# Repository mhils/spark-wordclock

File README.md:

spark-wordclock
===============

A Word Clock using the Spark Core.
https://community.spark.io/t/show-spark-wordclock-project/2347/

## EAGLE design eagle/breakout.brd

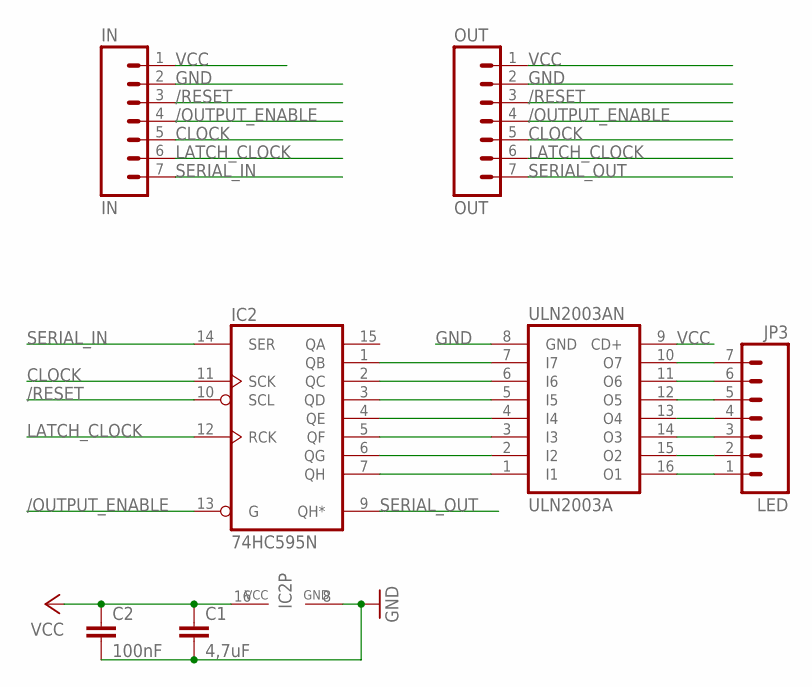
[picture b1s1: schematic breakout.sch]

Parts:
C1: 4,7uF; C025-024X044
C2: 100nF; C025-024X044
IC2: 74HC595N; DIL16
IN: IN; 1X07
JP3: LED; 1X07
OUT: OUT; 1X07
ULN2003A: ULN2003AN; DIL16

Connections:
/OUTPUT_ENABLE: IC2.13 (G), IN.4, OUT.4
/RESET: IC2.10 (SCL), IN.3, OUT.3
CLOCK: IC2.11 (SCK), IN.5, OUT.5
GND: C1.2, C2.2, IC2.8 (GND), IN.2, OUT.2, ULN2003A.8 (GND)
LATCH_CLOCK: IC2.12 (RCK), IN.6, OUT.6
unnamed: IC2.1 (QB), ULN2003A.7 (I7)
unnamed: IC2.2 (QC), ULN2003A.6 (I6)
unnamed: IC2.3 (QD), ULN2003A.5 (I5)
unnamed: IC2.4 (QE), ULN2003A.4 (I4)
unnamed: IC2.5 (QF), ULN2003A.3 (I3)
unnamed: IC2.6 (QG), ULN2003A.2 (I2)
unnamed: IC2.7 (QH), ULN2003A.1 (I1)
unnamed: JP3.7, ULN2003A.10 (O7)
unnamed: JP3.6, ULN2003A.11 (O6)
unnamed: JP3.5, ULN2003A.12 (O5)
unnamed: JP3.4, ULN2003A.13 (O4)
unnamed: JP3.3, ULN2003A.14 (O3)
unnamed: JP3.2, ULN2003A.15 (O2)
unnamed: JP3.1, ULN2003A.16 (O1)
SERIAL_IN: IC2.14 (SER), IN.7
SERIAL_OUT: IC2.9 (QH*), OUT.7
VCC: C1.1, C2.1, IC2.16 (VCC), IN.1, OUT.1, ULN2003A.9 (CD+)

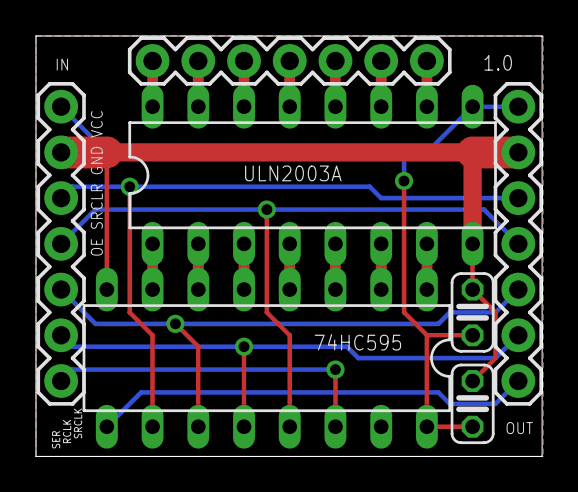
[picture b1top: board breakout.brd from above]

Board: 2 copper layers, 28.1 x 23.4 mm, 7 parts (0 on the bottom side), 22 nets.

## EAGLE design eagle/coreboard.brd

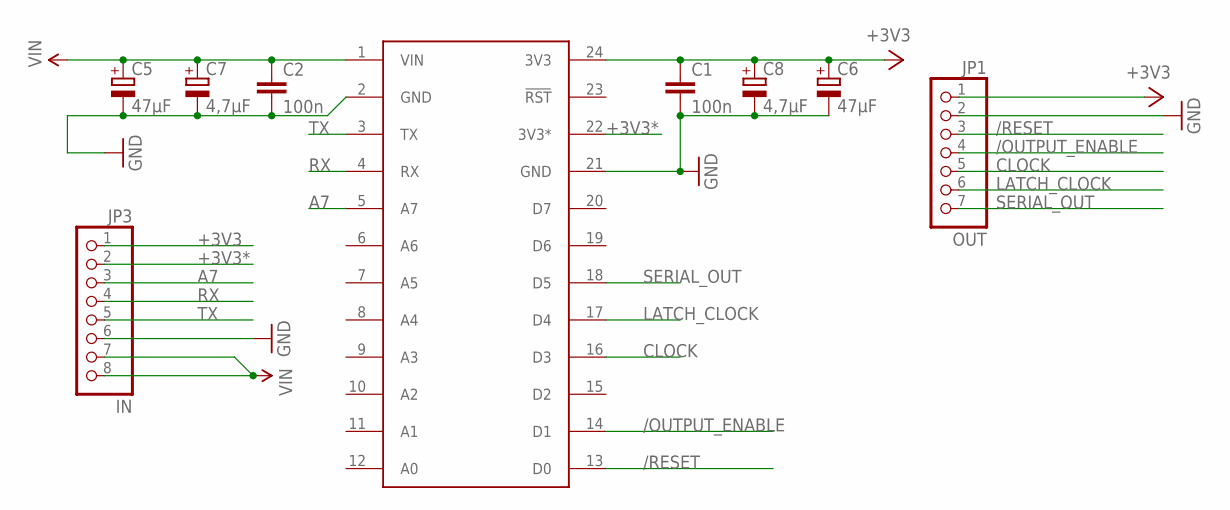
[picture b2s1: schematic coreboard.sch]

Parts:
C1, C2: 100n; C025-024X044
C5, C6: 47µF; E2,5-7
C7, C8: 4,7µF; E2,5-5
JP1: OUT; 1X07
JP3: IN; 1X08
U$1: SPARK_CORECORE; SPARK_CORE

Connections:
+3V3: C1.1, C6.+, C8.+, JP1.1, JP3.1, U$1.24 (3V3)
+3V3*: JP3.2, U$1.22 (3V3*)
/OUTPUT_ENABLE: JP1.4, U$1.14 (D1)
/RESET: JP1.3, U$1.13 (D0)
A7: JP3.3, U$1.5 (A7)
CLOCK: JP1.5, U$1.16 (D3)
GND: C1.2, C2.2, C5.-, C6.-, C7.-, C8.-, JP1.2, JP3.6, U$1.2 (GND), U$1.21 (GND)
LATCH_CLOCK: JP1.6, U$1.17 (D4)
RX: JP3.4, U$1.4 (RX)
SERIAL_OUT: JP1.7, U$1.18 (D5)
TX: JP3.5, U$1.3 (TX)
VIN: C2.1, C5.+, C7.+, JP3.7, JP3.8, U$1.1 (VIN)

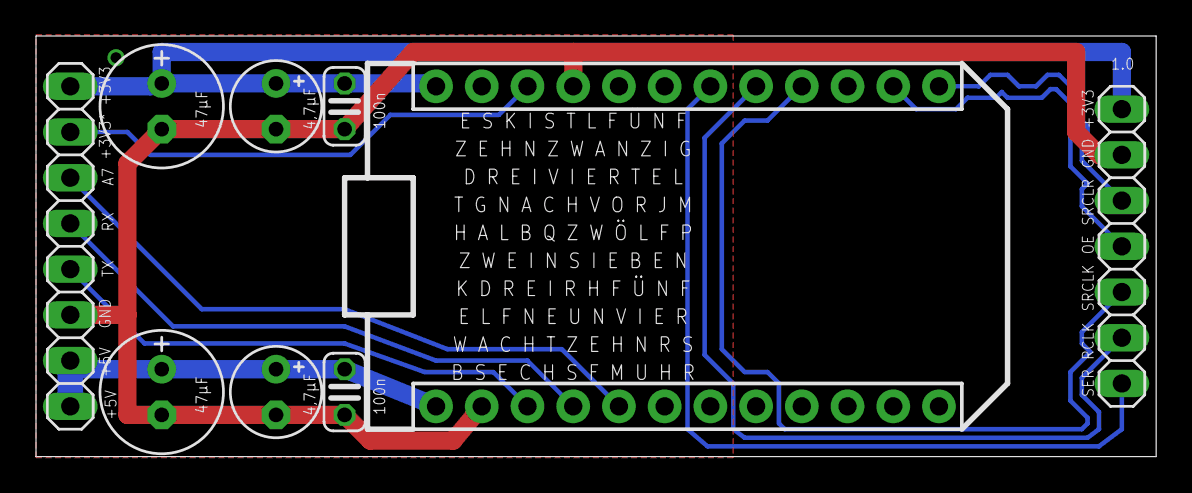
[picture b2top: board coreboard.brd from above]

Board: 2 copper layers, 62.2 x 23.4 mm, 9 parts (0 on the bottom side), 12 nets.

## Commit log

2014-03-28 add circuit board schematics
2014-03-30 update to latest version
2014-08-02 use Time library, employ brightness sensor
2019-10-27 add DST handling

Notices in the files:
parts and their libraries:
SparkFun-Connectors: Licensing: CC v3.0 Share-Alike You are welcome to use this library for commercial purposes.
